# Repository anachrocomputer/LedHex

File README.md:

# LedHex #

This repository contains several programs to run on an Arduino
and drive a display made from LEDs.

The display was made as a small-volume low-cost PCB using a design drawn in KiCad.

## KiCadV3Pcb ##

CAD files for the schematic and PCB,
designed in 2014 using KiCad V3.
This version of KiCad is so old now that it's not practical to update the files.
At the time of writing,
KiCad is at V8.0.5 and uses a completely different set of PCB footprints from V3.
So although it's possible to update the schematic files to use the latest format
and the latest symbols,
it's difficult to map those symbols to the new footprints.
This means that the PCB layout cannot be resynchronised with the schematic.
Probably the easiest way to fix this would be to re-draw in KiCad V8.

The schematic is shown as a PDF for reference when writing software
to drive the display.

## LedHexClock ##

Very simple four-digit clock with flashing colon.
So simple, in fact,
that there's no way to set the time.

TODO: add a way to set the time.

TODO: add 12/24 hour switch.

TODO: add other types of time display, TBD.

## LedHexCount4 ##

Display a four-digit counter on four LedHex PCBs connected in a chain.
Range is 0000-FFFF (0-65535).

## LedHexLampTest4 ##

Test a four-digit chain of LedHex PCBs by lighting up all the segments
in sequence.
This is also a test of the LED power supply!

## LedHexTest ##

Simply count 0-9, A-F repeatedly on a single digit display.

## LedHexTest4 ##

Test a four-digit chain of LedHex PCBs by lighting up all the segments
in sequence.

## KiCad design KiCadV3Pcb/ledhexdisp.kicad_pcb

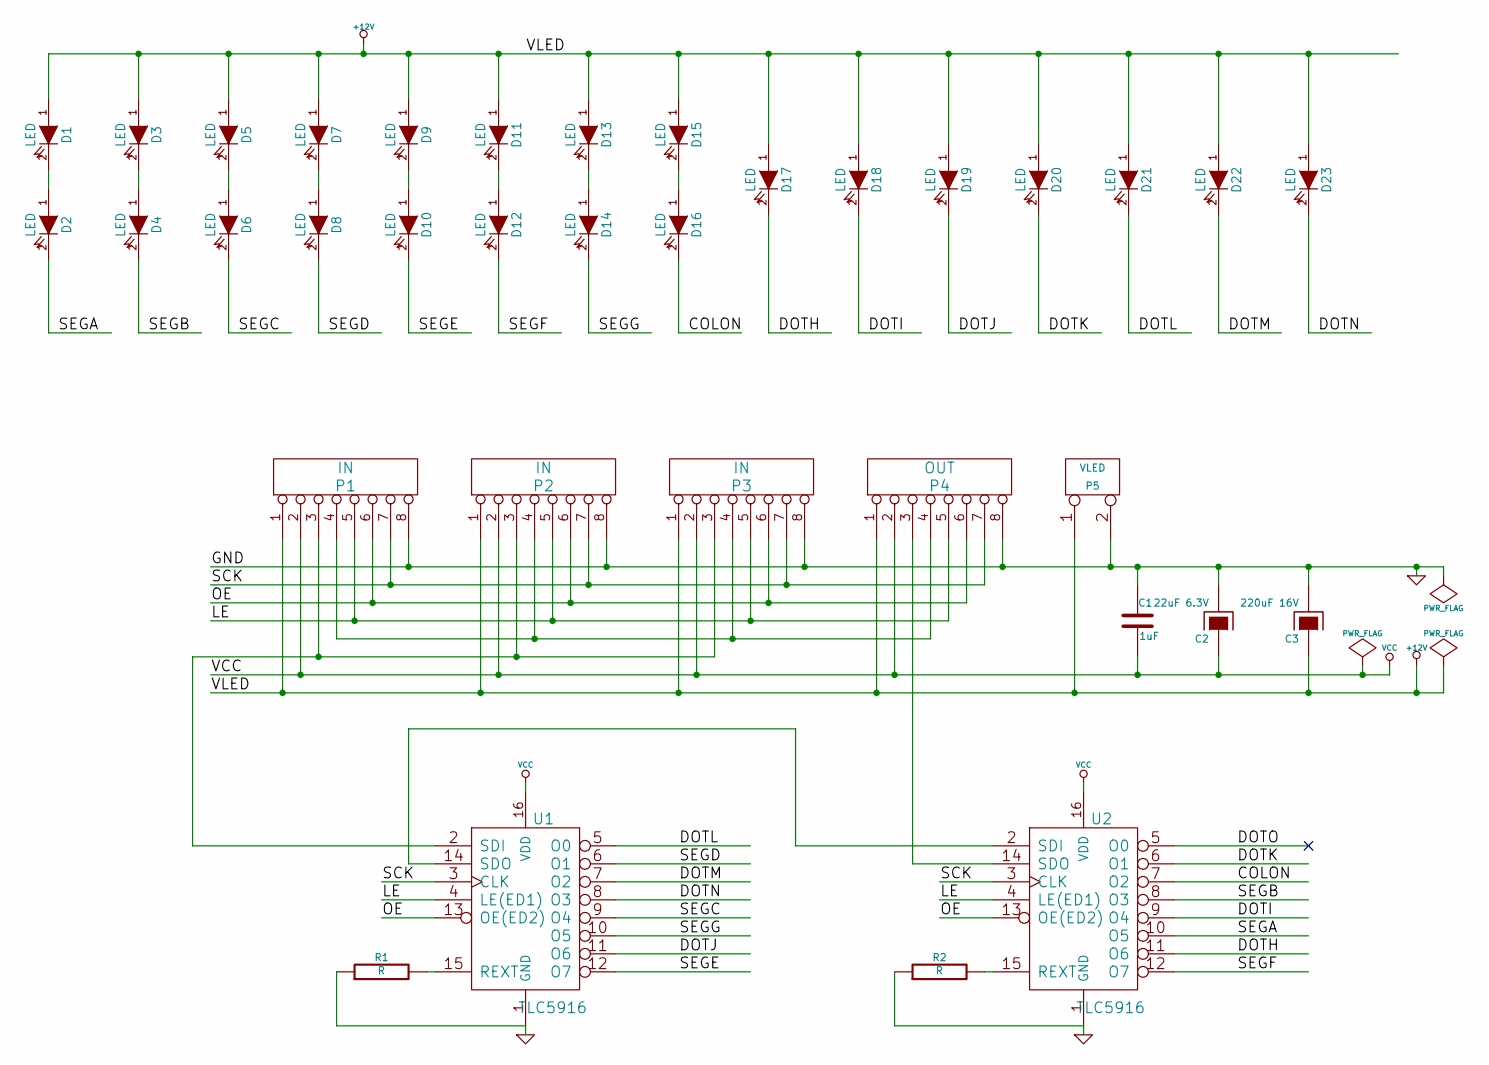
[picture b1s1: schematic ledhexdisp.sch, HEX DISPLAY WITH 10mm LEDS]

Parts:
C1: 1uF
C2: 22uF 6.3V
C3: 220uF 16V
D1, D2, D3, D4, D5, D6, D7, D8, D9, D10, D11, D12, D13, D14, D15, D16, D17, D18, D19, D20, D21, D22, D23: LED
P1, P2, P3: IN
P4: OUT
P5: VLED
R1, R2: R
U1, U2: TLC5916

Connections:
+12V: C3.1, D1.1 (A), D3.1 (A), D5.1 (A), D7.1 (A), D9.1 (A), D11.1 (A), D13.1 (A), D15.1 (A), D17.1 (A), D18.1 (A), D19.1 (A), D20.1 (A), D21.1 (A), D22.1 (A), D23.1 (A), P1.1, P2.1, P3.1, P4.1, P5.1
/COLON: D16.2 (K), U2.7 (O2)
/DOTH: D17.2 (K), U2.11 (O6)
/DOTI: D18.2 (K), U2.9 (O4)
/DOTJ: D19.2 (K), U1.11 (O6)
/DOTK: D20.2 (K), U2.6 (O1)
/DOTL: D21.2 (K), U1.5 (O0)
/DOTM: D22.2 (K), U1.7 (O2)
/DOTN: D23.2 (K), U1.8 (O3)
/LE: P1.5, P2.5, P3.5, P4.5, U1.4 (LE(ED1)), U2.4 (LE(ED1))
/OE: P1.6, P2.6, P3.6, P4.6, U1.13 (OE(ED2)), U2.13 (OE(ED2))
/SCK: P1.7, P2.7, P3.7, P4.7, U1.3 (CLK), U2.3 (CLK)
/SEGA: D2.2 (K), U2.10 (O5)
/SEGB: D4.2 (K), U2.8 (O3)
/SEGC: D6.2 (K), U1.9 (O4)
/SEGD: D8.2 (K), U1.6 (O1)
/SEGE: D10.2 (K), U1.12 (O7)
/SEGF: D12.2 (K), U2.12 (O7)
/SEGG: D14.2 (K), U1.10 (O5)
GND: C1.1, C2.2, C3.2, P1.8, P2.8, P3.8, P4.8, P5.2 (PM), R1.1, R2.1, U1.1 (GND), U2.1 (GND)
unnamed: D5.2 (K), D6.1 (A)
unnamed: D3.2 (K), D4.1 (A)
unnamed: R2.2, U2.15 (REXT)
unnamed: D15.2 (K), D16.1 (A)
unnamed: D13.2 (K), D14.1 (A)
unnamed: D11.2 (K), D12.1 (A)
unnamed: D9.2 (K), D10.1 (A)
unnamed: D7.2 (K), D8.1 (A)
unnamed: R1.2, U1.15 (REXT)
unnamed: P4.3, U2.14 (SDO)
unnamed: P1.3, P2.3, P3.3, U1.2 (SDI)
unnamed: U1.14 (SDO), U2.2 (SDI)
unnamed: P1.4, P2.4, P3.4, P4.4
unnamed: D1.2 (K), D2.1 (A)
VCC: C1.2, C2.1, P1.2, P2.2, P3.2, P4.2, U1.16 (VDD), U2.16 (VDD)

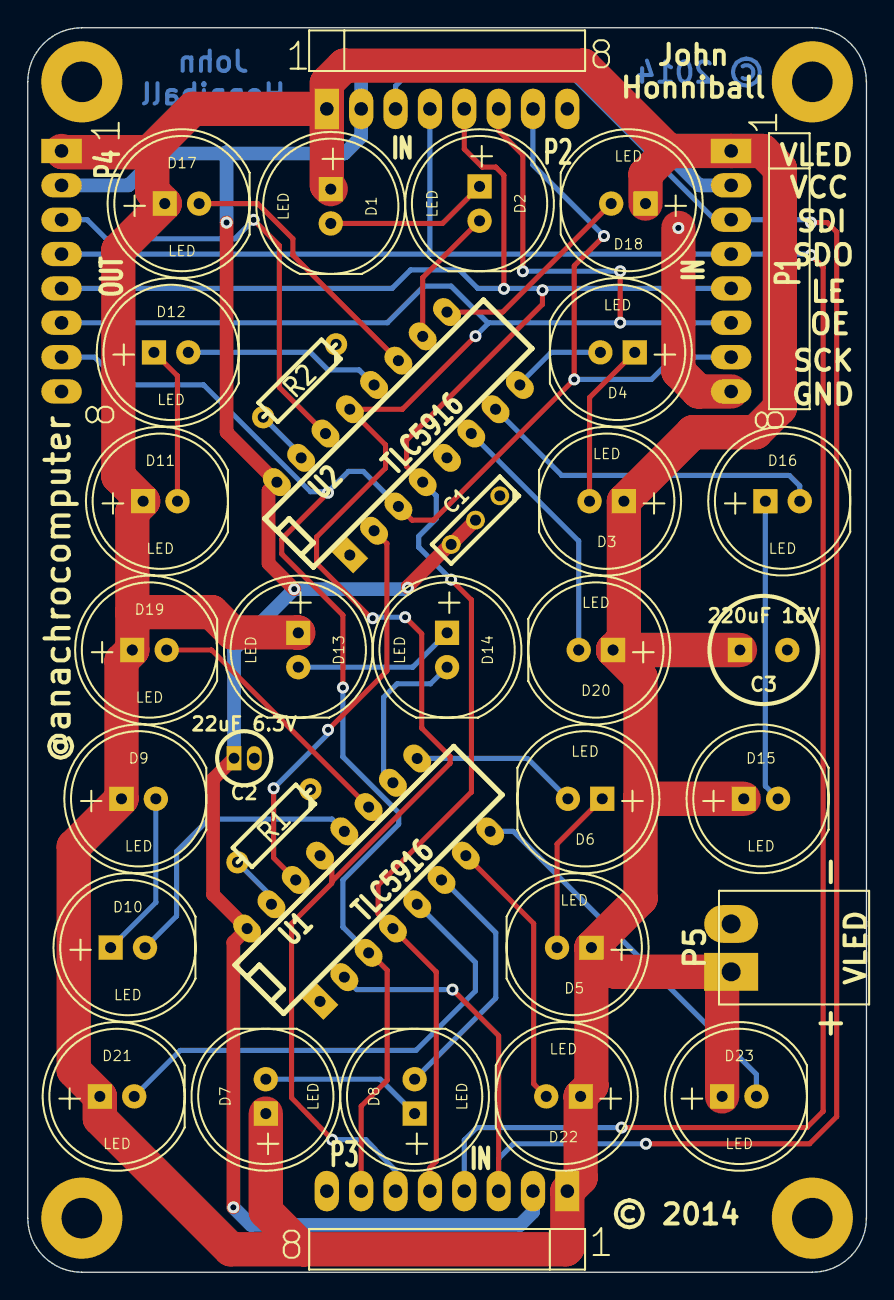
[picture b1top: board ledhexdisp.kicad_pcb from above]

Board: 2 copper layers, 62.0 x 92.0 mm, 35 parts (0 on the bottom side), 35 nets.

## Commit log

2018-02-16 Initial commit of test program for the LED hex display PCB. All it does is count up in hex 0-9, A-F continuously.
2018-02-16 Changes for new coding standards.
2018-02-17 Add some more test programs for the LED hex display PCB. All of these programs work on the 4-digit display (4 PCBs wired in a daisy-chain).
2018-02-18 Clean up code, add comments, modify for new coding standards.
2018-02-18 Clean up lamp test code, add comments, modify for new coding standards.
2018-02-18 Clean up counter code, add comments, modify for new coding standards.
2019-05-02 Add README in Markdown.
2024-03-14 Add LedHexClock.
    Embryonic Arduino sketch for a four-digit clock with flashing colon.
2024-03-14 Update README.
2024-10-20 Add KiCad PCB design files.
    At last, ten years after I designed it all. Shame it's now so old that it's almost no use. But the PCB layout can still be manufactured, if I need more boards.
2024-10-20 Add photo of PCB.
    Just the main digit with red LEDs.

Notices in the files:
KiCadV3Pcb/ledhexdisp.kicad_pcb:
© 2014
KiCadV3Pcb/ledhexdisp.sch:
Licence: GPL Open Hardware
